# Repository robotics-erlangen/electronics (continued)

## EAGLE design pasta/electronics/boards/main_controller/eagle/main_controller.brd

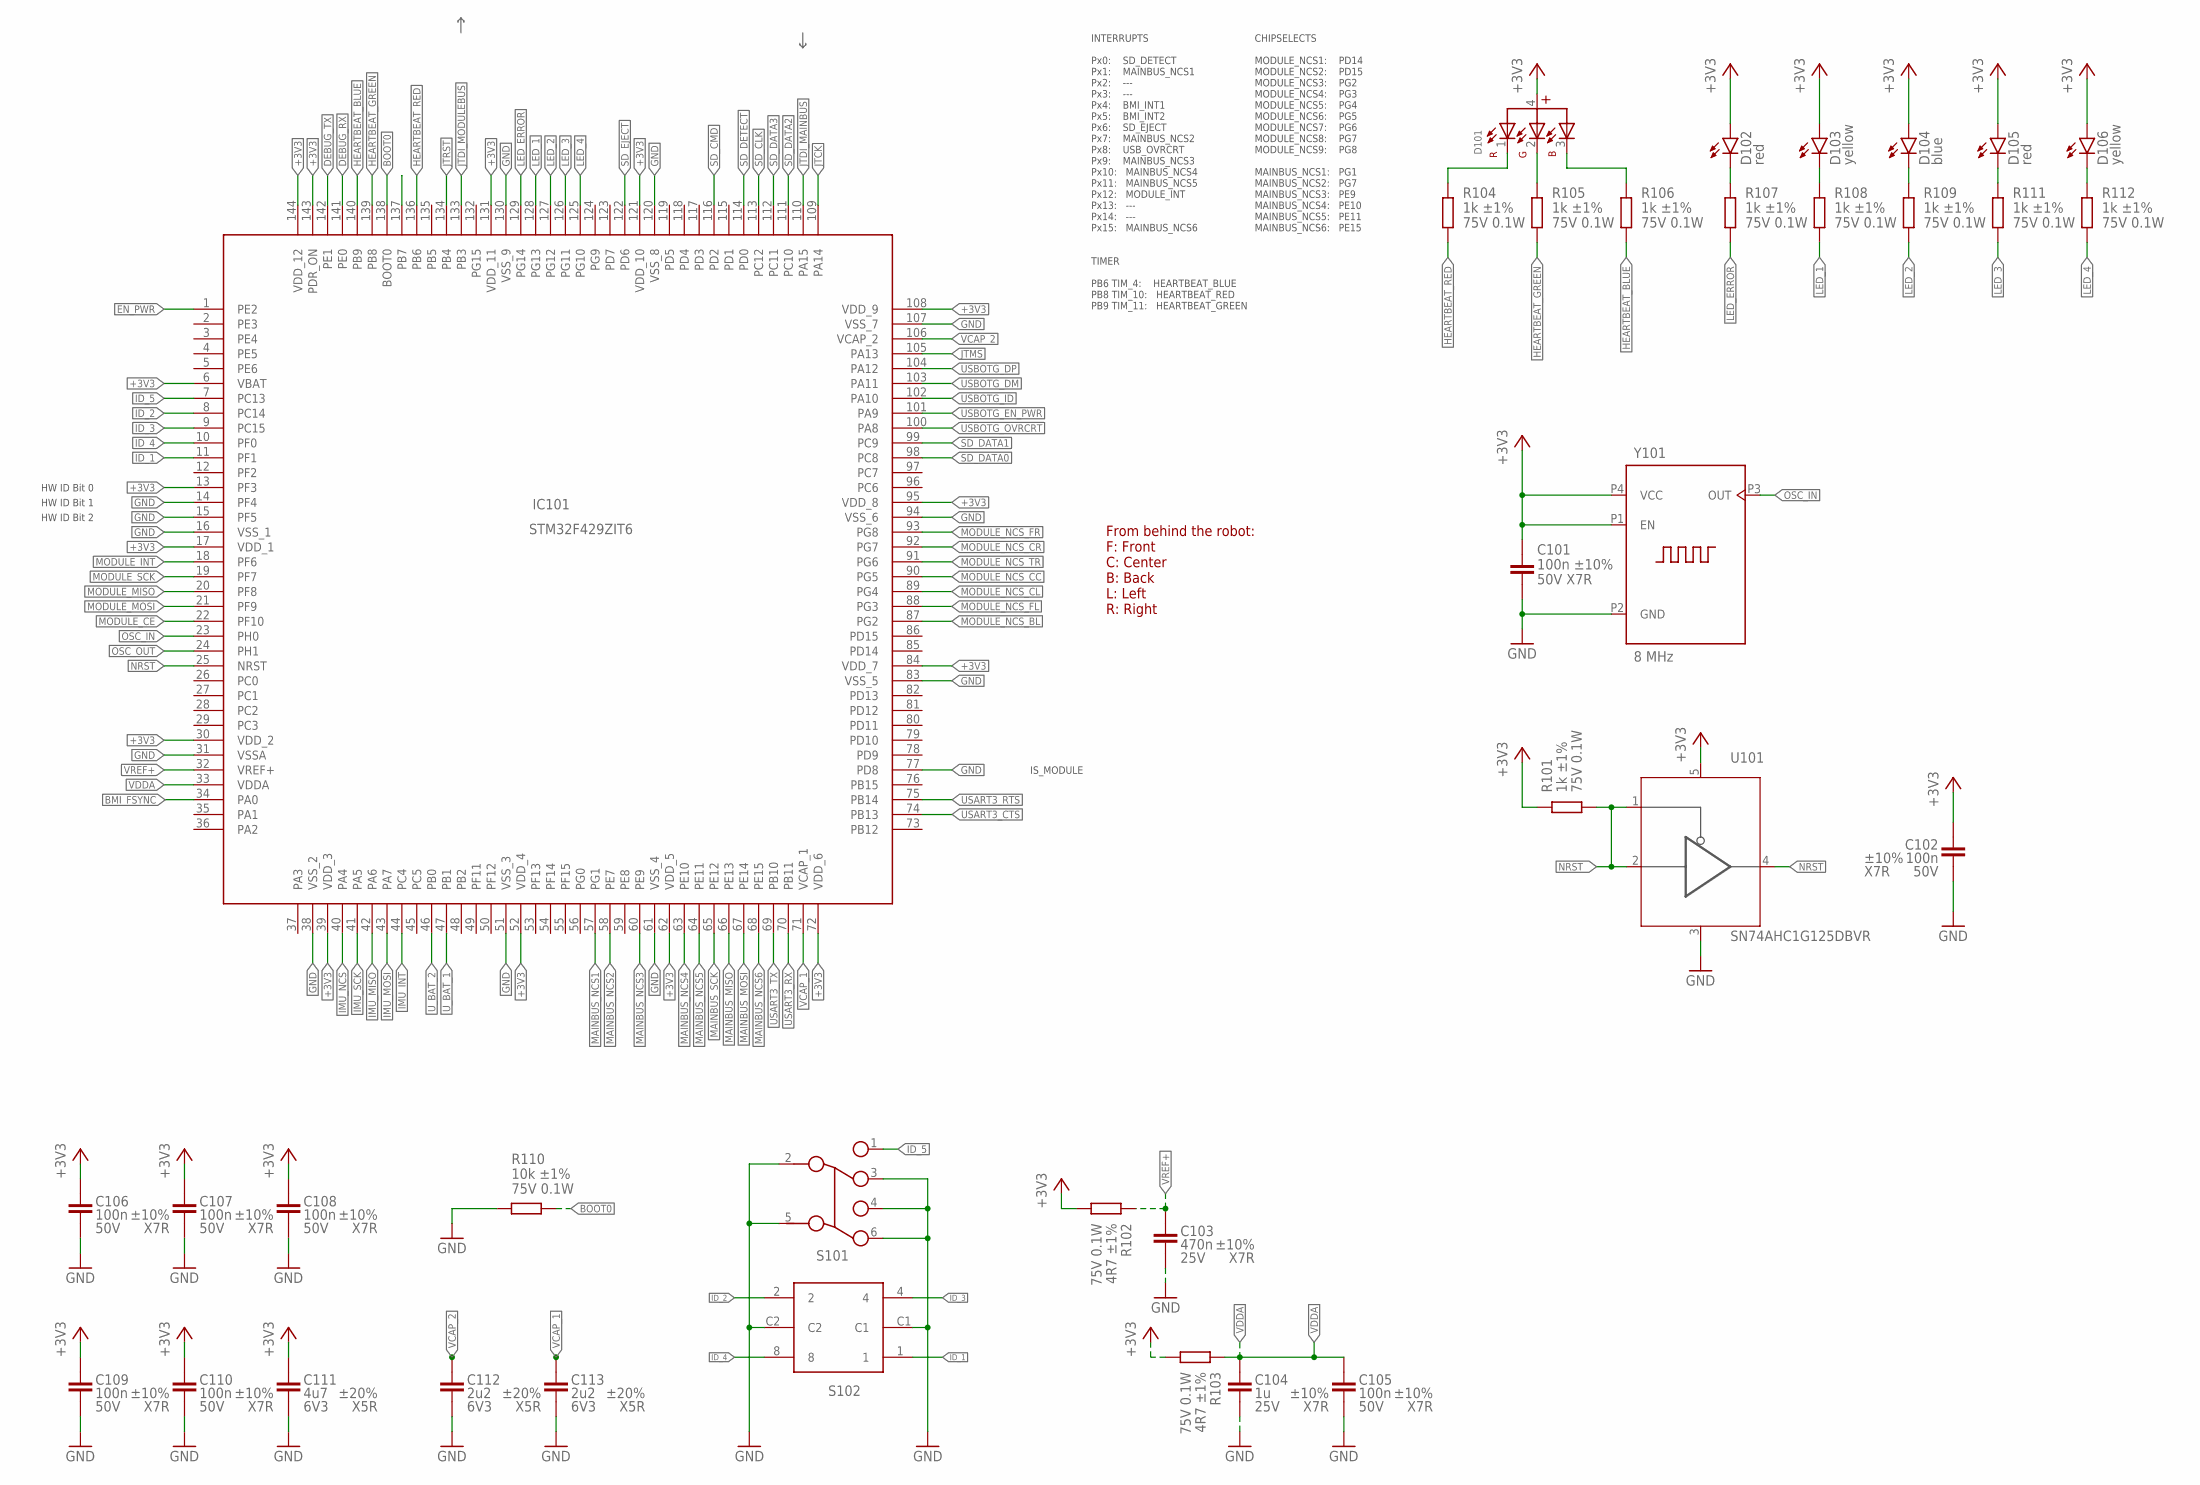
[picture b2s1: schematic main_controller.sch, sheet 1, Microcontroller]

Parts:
C101, C102, C105, C106, C107, C108, C109, C110: 100n ±10% 50V X7R; C0603
C103: 470n ±10% 25V X7R; C0603
C104: 1u ±10% 25V X7R; C0603
C111: 4u7 ±20% 6V3 X5R; C0603
C112, C113: 2u2 ±20% 6V3 X5R; C0603
D101: WL-SFCD_0606_150066M153000; WL-SFCX_0606
D102, D105: red; CHIPLED_0805
D103, D106: yellow; CHIPLED_0805
D104: blue; CHIPLED_0805
IC101: STM32F429ZIT6; QFP50P2200X2200X160-144N
R101, R104, R105, R106, R107, R108, R109, R111, R112: 1k ±1% 75V 0.1W; R0603
R102, R103: 4R7 ±1% 75V 0.1W; R0603
R110: 10k ±1% 75V 0.1W; R0603
S101: 452403012014
S102: 428542320816
U101: SN74AHC1G125DBVR; SOT23-5
Y101: 8 MHz; 830207192009

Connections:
+3V3: C101.1, C102.1, C106.1, C107.1, C108.1, C109.1, C110.1, C111.1, D101.4, D102.A, D103.A, D104.A, D105.A, D106.A, IC101.6 (VBAT), IC101.13 (PF3), IC101.17 (VDD_1), IC101.30 (VDD_2), IC101.39 (VDD_3), IC101.52 (VDD_4), IC101.62 (VDD_5), IC101.72 (VDD_6), IC101.84 (VDD_7), IC101.95 (VDD_8), IC101.108 (VDD_9), IC101.121 (VDD_10), IC101.131 (VDD_11), IC101.143 (PDR_ON), IC101.144 (VDD_12), R101.2, R102.1, R103.1, U101.5 (VCC), Y101.P1 (EN), Y101.P4 (VCC); also elsewhere on the board
BMI_FSYNC: IC101.34 (PA0); also elsewhere on the board
BOOT0: IC101.138 (BOOT0), R110.1
DEBUG_RX: IC101.141 (PE0); also elsewhere on the board
DEBUG_TX: IC101.142 (PE1); also elsewhere on the board
EN_PWR: IC101.1 (PE2); also elsewhere on the board
GND: C101.2, C102.2, C103.2, C104.2, C105.2, C106.2, C107.2, C108.2, C109.2, C110.2, C111.2, C112.2, C113.2, IC101.14 (PF4), IC101.15 (PF5), IC101.16 (VSS_1), IC101.31 (VSSA), IC101.38 (VSS_2), IC101.51 (VSS_3), IC101.61 (VSS_4), IC101.77 (PD8), IC101.83 (VSS_5), IC101.94 (VSS_6), IC101.107 (VSS_7), IC101.120 (VSS_8), IC101.130 (VSS_9), R110.2, S101.2, S101.3, S101.4, S101.5, S101.6, S102.C1, S102.C2, U101.3 (GND), Y101.P2 (GND); also elsewhere on the board
HEARTBEAT_BLUE: IC101.140 (PB9), R106.1
HEARTBEAT_GREEN: IC101.139 (PB8), R105.1
HEARTBEAT_RED: IC101.136 (PB6), R104.1
ID_1: IC101.11 (PF1), S102.1
ID_2: IC101.8 (PC14), S102.2
ID_3: IC101.9 (PC15), S102.4
ID_4: IC101.10 (PF0), S102.8
ID_5: IC101.7 (PC13), S101.1
IMU_INT: IC101.44 (PC4); also elsewhere on the board
IMU_MISO: IC101.42 (PA6); also elsewhere on the board
IMU_MOSI: IC101.43 (PA7); also elsewhere on the board
IMU_NCS: IC101.40 (PA4); also elsewhere on the board
IMU_SCK: IC101.41 (PA5); also elsewhere on the board
JTCK: IC101.109 (PA14); also elsewhere on the board
JTDI_MAINBUS: IC101.110 (PA15); also elsewhere on the board
JTDI_MODULEBUS: IC101.133 (PB3); also elsewhere on the board
JTMS: IC101.105 (PA13); also elsewhere on the board
JTRST: IC101.134 (PB4)
LED_1: IC101.128 (PG13), R108.1
LED_2: IC101.127 (PG12), R109.1
LED_3: IC101.126 (PG11), R111.1
LED_4: IC101.125 (PG10), R112.1
LED_ERROR: IC101.129 (PG14), R107.1
MAINBUS_MISO: IC101.66 (PE13); also elsewhere on the board
MAINBUS_MOSI: IC101.67 (PE14); also elsewhere on the board
MAINBUS_NCS1: IC101.57 (PG1); also elsewhere on the board
MAINBUS_NCS2: IC101.58 (PE7); also elsewhere on the board
MAINBUS_NCS3: IC101.60 (PE9); also elsewhere on the board
MAINBUS_NCS4: IC101.63 (PE10); also elsewhere on the board
MAINBUS_NCS5: IC101.64 (PE11); also elsewhere on the board
MAINBUS_NCS6: IC101.68 (PE15); also elsewhere on the board
MAINBUS_SCK: IC101.65 (PE12); also elsewhere on the board
MODULE_CE: IC101.22 (PF10)
MODULE_INT: IC101.18 (PF6); also elsewhere on the board
MODULE_MISO: IC101.20 (PF8); also elsewhere on the board
MODULE_MOSI: IC101.21 (PF9); also elsewhere on the board
MODULE_NCS_BL: IC101.87 (PG2); also elsewhere on the board
MODULE_NCS_CC: IC101.90 (PG5); also elsewhere on the board
MODULE_NCS_CL: IC101.89 (PG4); also elsewhere on the board
MODULE_NCS_CR: IC101.92 (PG7); also elsewhere on the board
MODULE_NCS_FL: IC101.88 (PG3); also elsewhere on the board
MODULE_NCS_FR: IC101.93 (PG8); also elsewhere on the board
MODULE_NCS_TR: IC101.91 (PG6); also elsewhere on the board
MODULE_SCK: IC101.19 (PF7); also elsewhere on the board
unnamed: D102.C, R107.2
unnamed: D103.C, R108.2
unnamed: D104.C, R109.2
unnamed: D101.1 (R), R104.2
unnamed: D101.2 (G), R105.2
unnamed: D101.3 (B), R106.2
unnamed: D105.C, R111.2
unnamed: D106.C, R112.2
NRST: IC101.25 (NRST), U101.4 (O); also elsewhere on the board
NRST_: R101.1, U101.1 (OE), U101.2 (I); also elsewhere on the board
OSC_IN: IC101.23 (PH0), Y101.P3 (OUT)
OSC_OUT: IC101.24 (PH1)
SD_CLK: IC101.113 (PC12); also elsewhere on the board
SD_CMD: IC101.116 (PD2); also elsewhere on the board
SD_DATA0: IC101.98 (PC8); also elsewhere on the board
SD_DATA1: IC101.99 (PC9); also elsewhere on the board
SD_DATA2: IC101.111 (PC10); also elsewhere on the board
SD_DATA3: IC101.112 (PC11); also elsewhere on the board
SD_DETECT: IC101.114 (PD0); also elsewhere on the board
SD_EJECT: IC101.122 (PD6); also elsewhere on the board
USART3_CTS: IC101.74 (PB13); also elsewhere on the board
USART3_RTS: IC101.75 (PB14); also elsewhere on the board
USART3_RX: IC101.70 (PB11); also elsewhere on the board
USART3_TX: IC101.69 (PB10); also elsewhere on the board
USBOTG_DM: IC101.103 (PA11); also elsewhere on the board
USBOTG_DP: IC101.104 (PA12); also elsewhere on the board
USBOTG_EN_PWR: IC101.101 (PA9); also elsewhere on the board
USBOTG_ID: IC101.102 (PA10)
USBOTG_OVRCRT: IC101.100 (PA8); also elsewhere on the board
U_BAT_1: IC101.47 (PB1); also elsewhere on the board
U_BAT_2: IC101.46 (PB0); also elsewhere on the board
VCAP_1: C113.1, IC101.71 (VCAP_1)
VCAP_2: C112.1, IC101.106 (VCAP_2)
VDDA: C104.1, C105.1, IC101.33 (VDDA), R103.2
VREF+: C103.1, IC101.32 (VREF+), R102.2

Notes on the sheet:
HW ID Bit 0
HW ID Bit 1
HW ID Bit 2
IS_MODULE
INTERRUPTS Px0: SD_DETECT Px1: MAINBUS_NCS1 Px2: --- Px3: --- Px4: BMI_INT1 Px5: BMI_INT2 Px6: SD_EJECT Px7: MAINBUS_NCS2 Px8: USB_OVRCRT Px9: MAINBUS_NCS3 Px10: MAINBUS_NCS4 Px11: MAINBUS_NCS5 Px12: MODULE_INT Px13: --- Px14: --- Px15: MAINBUS_NCS6
TIMER PB6 TIM_4: HEARTBEAT_BLUE PB8 TIM_10: HEARTBEAT_RED PB9 TIM_11: HEARTBEAT_GREEN
CHIPSELECTS MODULE_NCS1: PD14 MODULE_NCS2: PD15 MODULE_NCS3: PG2 MODULE_NCS4: PG3 MODULE_NCS5: PG4 MODULE_NCS6: PG5 MODULE_NCS7: PG6 MODULE_NCS8: PG7 MODULE_NCS9: PG8 MAINBUS_NCS1: PG1 MAINBUS_NCS2: PG7 MAINBUS_NCS3: PE9 MAINBUS_NCS4: PE10 MAINBUS_NCS5: PE11 MAINBUS_NCS6: PE15
From behind the robot: F: Front C: Center B: Back L: Left R: Right

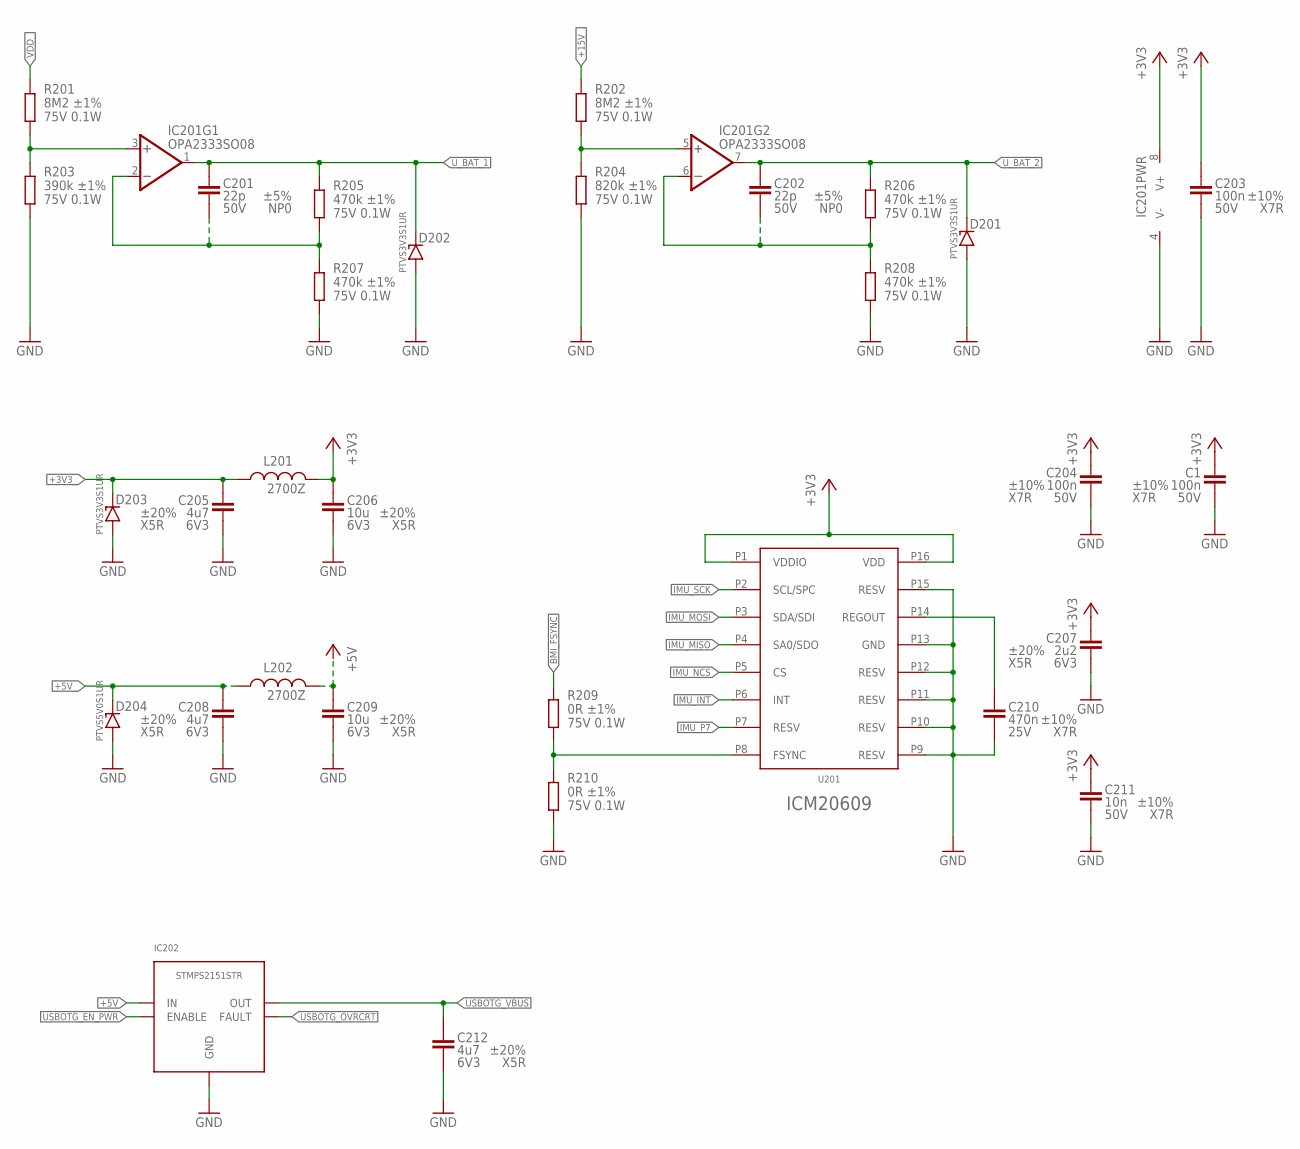
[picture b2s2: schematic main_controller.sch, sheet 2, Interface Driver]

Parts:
C1, C203, C204: 100n ±10% 50V X7R; C0603
C201, C202: 22p ±5% 50V NP0; C0603
C205, C208, C212: 4u7 ±20% 6V3 X5R; C0603
C206, C209: 10u ±20% 6V3 X5R; C0603
C207: 2u2 ±20% 6V3 X5R; C0603
C210: 470n ±10% 25V X7R; C0603
C211: 10n ±10% 50V X7R; C0603
D201, D202, D203: PTVS3V3S1UR; SOD123
D204: PTVS5V0S1UR; SOD123
IC201: OPA2333SO08; SO08; MPN OPA2333AIDR; MOUSER 595-OPA2333AIDR
IC202: STMPS2151STR; SOT23-5:1
L201, L202: 2700Z; WE-CBF_0603(W=2.6)
R201, R202: 8M2 ±1% 75V 0.1W; R0603
R203: 390k ±1% 75V 0.1W; R0603
R204: 820k ±1% 75V 0.1W; R0603
R205, R206, R207, R208: 470k ±1% 75V 0.1W; R0603
R209, R210: 0R ±1% 75V 0.1W; R0603
U201: ICM20609

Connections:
+3V3: C1.1, C203.1, C204.1, C206.1, C207.1, C211.1, IC201.8 (V+), L201.1, U201.P1 (VDDIO), U201.P16 (VDD); also elsewhere on the board
+3V3_: C205.1, D203.C (KATHODE), L201.2; also elsewhere on the board
+5V: C209.1, IC202.5 (IN), L202.1
+5V_: C208.1, D204.C (KATHODE), L202.2; also elsewhere on the board
+15V_: R202.2; also elsewhere on the board
BMI_FSYNC: R209.2; also elsewhere on the board
GND: C1.2, C203.2, C204.2, C205.2, C206.2, C207.2, C208.2, C209.2, C210.2, C211.2, C212.2, D201.A (ANODE), D202.A (ANODE), D203.A (ANODE), D204.A (ANODE), IC201.4 (V-), IC202.2 (GND), R203.1, R204.1, R207.1, R208.1, R210.1, U201.P9 (RESV), U201.P10 (RESV), U201.P11 (RESV), U201.P12 (RESV), U201.P13 (GND), U201.P15 (RESV); also elsewhere on the board
IMU_INT: U201.P6 (INT); also elsewhere on the board
IMU_MISO: U201.P4 (SA0/SDO); also elsewhere on the board
IMU_MOSI: U201.P3 (SDA/SDI); also elsewhere on the board
IMU_NCS: U201.P5 (CS); also elsewhere on the board
IMU_P7: U201.P7 (RESV)
IMU_SCK: U201.P2 (SCL/SPC); also elsewhere on the board
unnamed: IC201.3 (+IN), R201.1, R203.2
unnamed: C201.2, IC201.2 (-IN), R205.1, R207.2
unnamed: C202.2, IC201.6 (-IN), R206.1, R208.2
unnamed: IC201.5 (+IN), R202.1, R204.2
unnamed: R209.1, R210.2, U201.P8 (FSYNC)
unnamed: C210.1, U201.P14 (REGOUT)
USBOTG_EN_PWR: IC202.4 (ENABLE); also elsewhere on the board
USBOTG_OVRCRT: IC202.3 (FAULT); also elsewhere on the board
USBOTG_VBUS: C212.1, IC202.1 (OUT); also elsewhere on the board
U_BAT_1: C201.1, D202.C (KATHODE), IC201.1 (OUT), R205.2; also elsewhere on the board
U_BAT_2: C202.1, D201.C (KATHODE), IC201.7 (OUT), R206.2; also elsewhere on the board
VDD_: R201.2; also elsewhere on the board

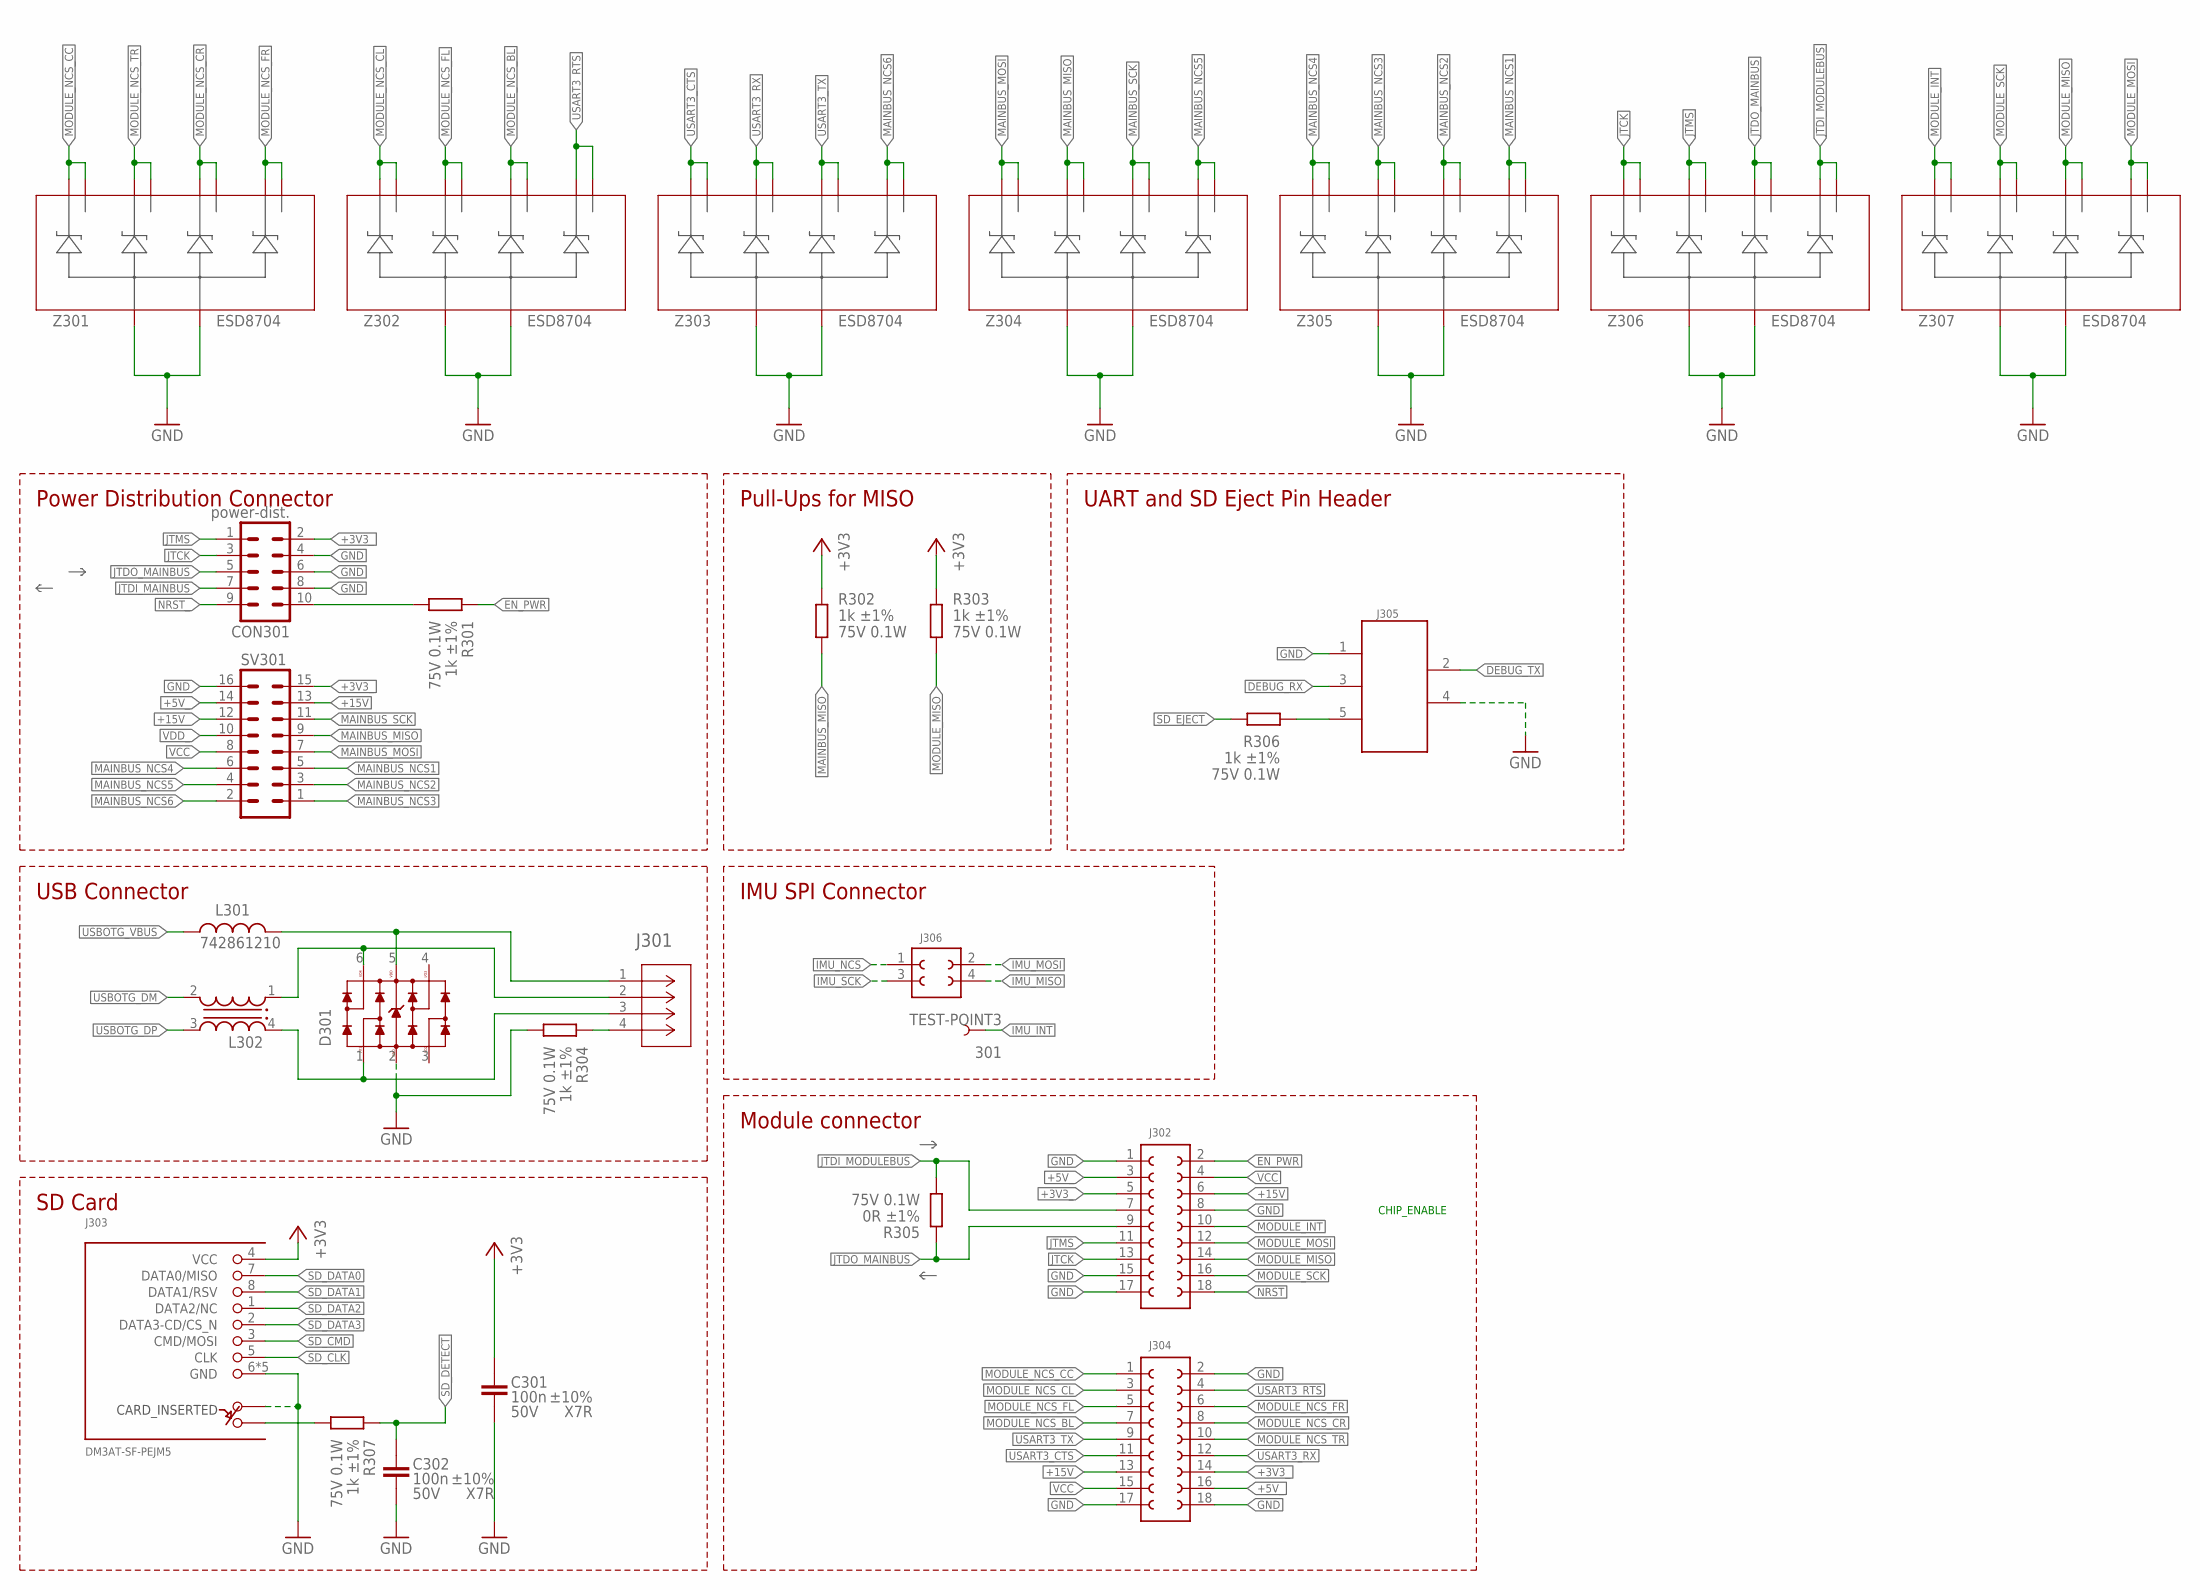
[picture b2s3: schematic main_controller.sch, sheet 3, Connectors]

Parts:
301: TEST-POINT3; PAD.03X.03
C301, C302: 100n ±10% 50V X7R; C0603
CON301: power-dist.; MA05-2; MPN 61301021121
D301: WE-TVS_824001; WE-TVS_SOT23-6L
J301: 530480410; CON_530480410_MOL
J302, J304: 610018243021; 610X1821821
J303: DM3AT-SF-PEJM5; MPN DM3AT-SF-PEJM5; MOUSER 798-DM3AT-SF-PEJM5
J305: 61000618221
J306: 623X0421021
L301: 742861210; WE-CBF_0603(W=2.6)
L302: WE-CNSW_1206_744232090; WE-CNSW_1206
R301, R302, R303, R304, R306, R307: 1k ±1% 75V 0.1W; R0603
R305: 0R ±1% 75V 0.1W; R0603
SV301: MA08-2
Z301, Z302, Z303, Z304, Z305, Z306, Z307: ESD8704; UDFN10

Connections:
+3V3: C301.1, J303.4 (VCC), R302.2, R303.2; also elsewhere on the board
+3V3_: CON301.2, J302.5 (3), J304.14 (12), SV301.15; also elsewhere on the board
+5V_: J302.3 (2), J304.16 (11), SV301.14; also elsewhere on the board
+15V: J302.6 (16), J304.13 (7), SV301.13
+15V_: SV301.12; also elsewhere on the board
DEBUG_RX: J305.3; also elsewhere on the board
DEBUG_TX: J305.2; also elsewhere on the board
EN_PWR: J302.2 (18), R301.2; also elsewhere on the board
GND: C301.2, C302.2, CON301.4, CON301.6, CON301.8, D301.2 (GND), J302.1, J302.8 (15), J302.15 (8), J302.17 (9), J303.6 (GND), J303.A, J303.MOUNT0 (GND), J303.MOUNT1 (GND), J303.MOUNT2 (GND), J303.MOUNT3 (GND), J304.2 (18), J304.17 (9), J304.18 (10), J305.1, J305.4, R304.1, SV301.16, Z301.3 (A), Z301.8 (A), Z302.3 (A), Z302.8 (A), Z303.3 (A), Z303.8 (A), Z304.3 (A), Z304.8 (A), Z305.3 (A), Z305.8 (A), Z306.3 (A), Z306.8 (A), Z307.3 (A), Z307.8 (A); also elsewhere on the board
IMU_INT: 301.P$1; also elsewhere on the board
IMU_MISO: J306.4 (3); also elsewhere on the board
IMU_MOSI: J306.2 (4); also elsewhere on the board
IMU_NCS: J306.1; also elsewhere on the board
IMU_SCK: J306.3 (2); also elsewhere on the board
JTCK: CON301.3, J302.13 (7), Z306.1 (C1), Z306.10 (D1); also elsewhere on the board
JTDI_MAINBUS: CON301.7; also elsewhere on the board
JTDI_MODULEBUS: J302.7 (4), R305.1, Z306.5 (C4), Z306.6 (D4); also elsewhere on the board
JTDO_MAINBUS: CON301.5, J302.9 (5), R305.2, Z306.4 (C3), Z306.7 (D3)
JTMS: CON301.1, J302.11 (6), Z306.2 (C2), Z306.9 (D2); also elsewhere on the board
MAINBUS_MISO: R302.1, SV301.9, Z304.2 (C2), Z304.9 (D2); also elsewhere on the board
MAINBUS_MOSI: SV301.7, Z304.1 (C1), Z304.10 (D1); also elsewhere on the board
MAINBUS_NCS1: SV301.5, Z305.5 (C4), Z305.6 (D4); also elsewhere on the board
MAINBUS_NCS2: SV301.3, Z305.4 (C3), Z305.7 (D3); also elsewhere on the board
MAINBUS_NCS3: SV301.1, Z305.2 (C2), Z305.9 (D2); also elsewhere on the board
MAINBUS_NCS4: SV301.6, Z305.1 (C1), Z305.10 (D1); also elsewhere on the board
MAINBUS_NCS5: SV301.4, Z304.5 (C4), Z304.6 (D4); also elsewhere on the board
MAINBUS_NCS6: SV301.2, Z303.5 (C4), Z303.6 (D4); also elsewhere on the board
MAINBUS_SCK: SV301.11, Z304.4 (C3), Z304.7 (D3); also elsewhere on the board
MODULE_INT: J302.10 (14), Z307.1 (C1), Z307.10 (D1); also elsewhere on the board
MODULE_MISO: J302.14 (12), R303.1, Z307.4 (C3), Z307.7 (D3); also elsewhere on the board
MODULE_MOSI: J302.12 (13), Z307.5 (C4), Z307.6 (D4); also elsewhere on the board
MODULE_NCS_BL: J304.7 (4), Z302.4 (C3), Z302.7 (D3); also elsewhere on the board
MODULE_NCS_CC: J304.1, Z301.1 (C1), Z301.10 (D1); also elsewhere on the board
MODULE_NCS_CL: J304.3 (2), Z302.1 (C1), Z302.10 (D1); also elsewhere on the board
MODULE_NCS_CR: J304.8 (15), Z301.4 (C3), Z301.7 (D3); also elsewhere on the board
MODULE_NCS_FL: J304.5 (3), Z302.2 (C2), Z302.9 (D2); also elsewhere on the board
MODULE_NCS_FR: J304.6 (16), Z301.5 (C4), Z301.6 (D4); also elsewhere on the board
MODULE_NCS_TR: J304.10 (14), Z301.2 (C2), Z301.9 (D2); also elsewhere on the board
MODULE_SCK: J302.16 (11), Z307.2 (C2), Z307.9 (D2); also elsewhere on the board
unnamed: CON301.10, R301.1
unnamed: D301.6, J301.2, L302.1 (4)
unnamed: J305.5, R306.1
unnamed: J301.4, R304.2
unnamed: D301.1, J301.3, L302.4 (1)
unnamed: D301.5 (VDD), J301.1, L301.2
NRST: J302.18 (10); also elsewhere on the board
NRST_: CON301.9; also elsewhere on the board
SD_CARD_DETECT_GND: J303.B, R307.1
SD_CLK: J303.5 (CLK); also elsewhere on the board
SD_CMD: J303.3 (CMD/MOSI); also elsewhere on the board
SD_DATA0: J303.7 (DATA0/MISO); also elsewhere on the board
SD_DATA1: J303.8 (DATA1/RSV); also elsewhere on the board
SD_DATA2: J303.1 (DATA2/NC); also elsewhere on the board
SD_DATA3: J303.2 (DATA3-CD/CS_N); also elsewhere on the board
SD_DETECT: C302.1, R307.2; also elsewhere on the board
SD_EJECT: R306.2; also elsewhere on the board
USART3_CTS: J304.11 (6), Z303.1 (C1), Z303.10 (D1); also elsewhere on the board
USART3_RTS: J304.4 (17), Z302.5 (C4), Z302.6 (D4); also elsewhere on the board
USART3_RX: J304.12 (13), Z303.2 (C2), Z303.9 (D2); also elsewhere on the board
USART3_TX: J304.9 (5), Z303.4 (C3), Z303.7 (D3); also elsewhere on the board
USBOTG_DM: L302.2 (3); also elsewhere on the board
USBOTG_DP: L302.3 (2); also elsewhere on the board
USBOTG_VBUS: L301.1; also elsewhere on the board
VCC: J302.4 (17), J304.15 (8), SV301.8
VDD_: SV301.10; also elsewhere on the board

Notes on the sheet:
SD Card
Power Distribution Connector
USB Connector
CHIP_ENABLE
Module connector
Pull-Ups for MISO
UART and SD Eject Pin Header
IMU SPI Connector
